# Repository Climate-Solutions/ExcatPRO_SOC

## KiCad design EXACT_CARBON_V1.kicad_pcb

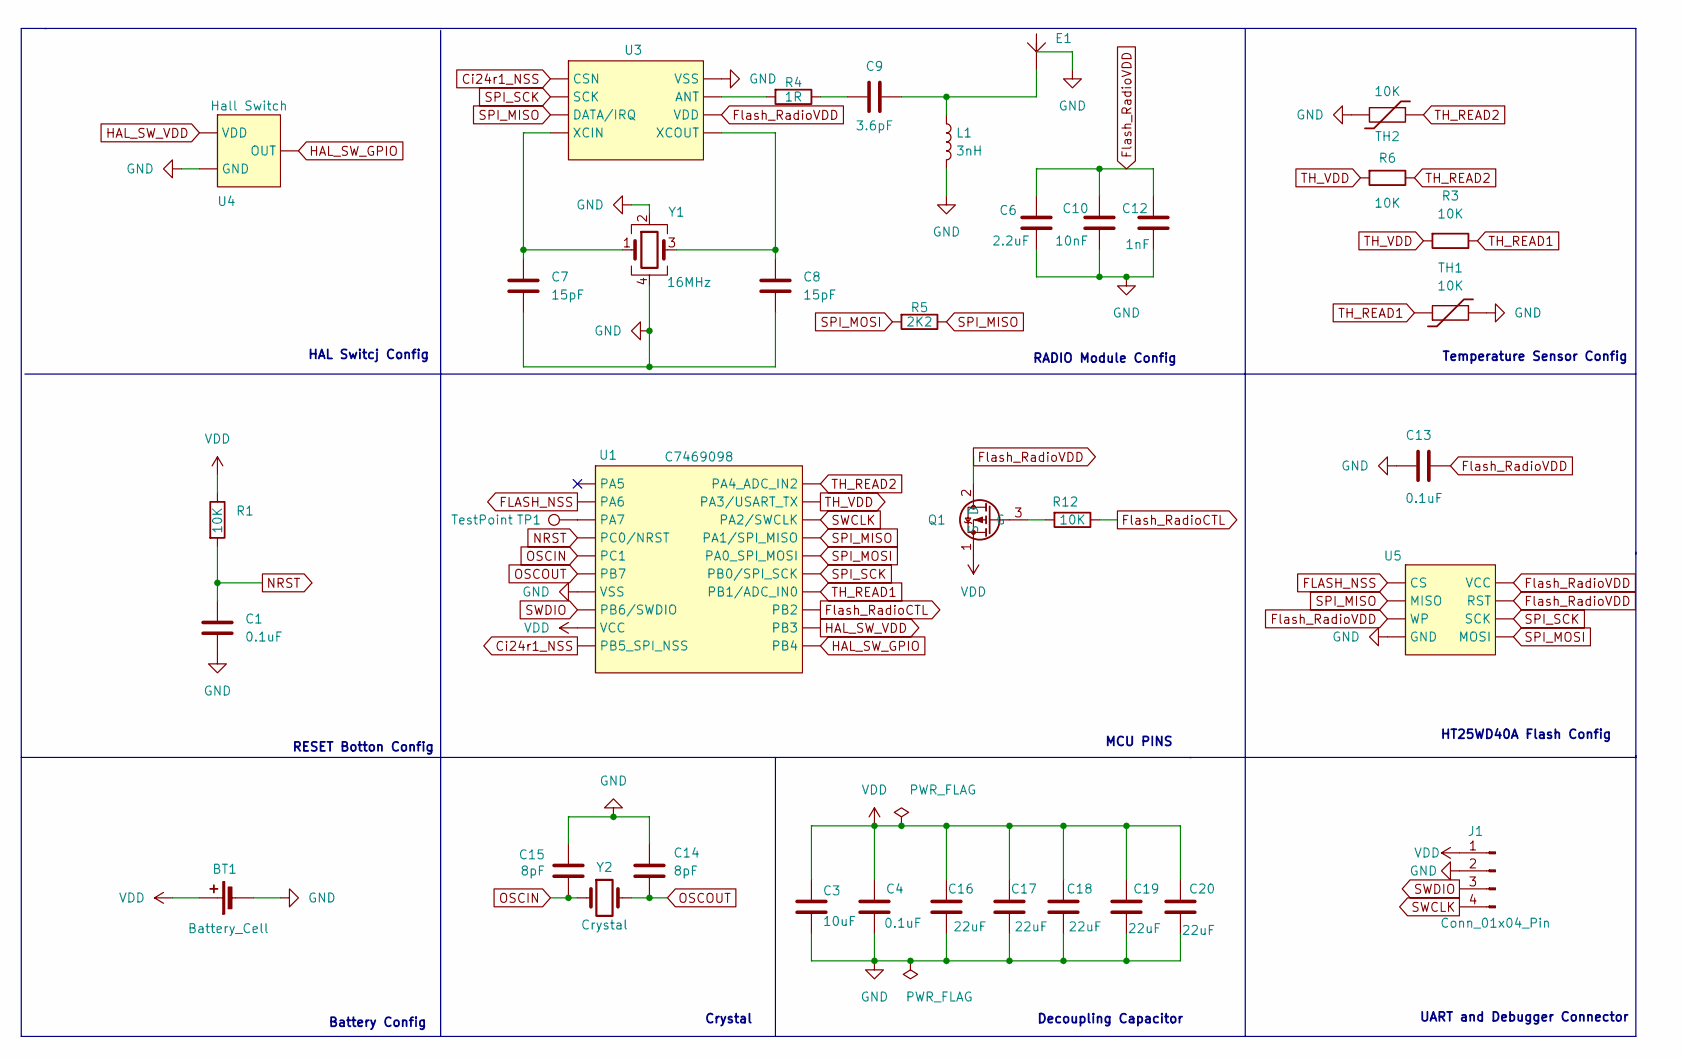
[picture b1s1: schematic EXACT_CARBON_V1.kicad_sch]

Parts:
BT1: Battery_Cell; CR2
C1, C4, C13: 0.1uF; C_0402_1005Metric_Pad0.74x0.62mm_HandSolder
C3: 10uF; C_0402_1005Metric_Pad0.74x0.62mm_HandSolder
C6: 2.2uF; C_0402_1005Metric_Pad0.74x0.62mm_HandSolder
C7, C8: 15pF; C_0402_1005Metric_Pad0.74x0.62mm_HandSolder
C9: 3.6pF; C_0402_1005Metric_Pad0.74x0.62mm_HandSolder
C10: 10nF; C_0402_1005Metric_Pad0.74x0.62mm_HandSolder
C12: 1nF; C_0402_1005Metric_Pad0.74x0.62mm_HandSolder
C14, C15: 8pF; C_0402_1005Metric_Pad0.74x0.62mm_HandSolder
C16, C17, C18, C19, C20: 22uF; C_0805_2012Metric
E1: PCB_Trace
J1: Conn_01x04_Pin; PinHeader_1x04_P2.00mm_Vertical
L1: 3nH; L_0402_1005Metric_Pad0.77x0.64mm_HandSolder
Q1: SOT-23
R1, R3, R6, R12: 10K; R_0402_1005Metric_Pad0.72x0.64mm_HandSolder
R4: 1R; R_0402_1005Metric
R5: 2K2; R_0402_1005Metric
TH1, TH2: 10K; R_0402_1005Metric_Pad0.72x0.64mm_HandSolder
TP1: TestPoint; TestPoint_Pad_D1.0mm
U1: C7469098; TSSOP-20_4.4x6.5mm_P0.65mm
U3: Ci24r1
U4: Hall Switch; HAL2041SO
U5: SOP-8_3.9x4.9mm_P1.27mm
Y1: 16MHz; Crystal_SMD_3225-4Pin_3.2x2.5mm
Y2: Crystal; Crystal_SMD_EuroQuartz_EQ161-2Pin_3.2x1.5mm

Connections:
Ci24r1_NSS: U1.10 (PB5_SPI_NSS), U3.1 (CSN)
FLASH_NSS: U1.2 (PA6), U5.1 (CS)
Flash_RadioCTL: R12.1, U1.13 (PB2)
Flash_RadioVDD: C6.1, C10.1, C12.1, C13.2, Q1.2 (D), U3.6 (VDD), U5.3 (WP), U5.7 (RST), U5.8 (VCC)
GND: BT1.2 (-), C1.2, C3.2, C4.2, C6.2, C7.2, C8.2, C10.2, C12.2, C13.1, C14.1, C15.1, C16.2, C17.2, C18.2, C19.2, C20.2, E1.1 (GND), J1.2, L1.2, TH1.2, TH2.2, U1.7 (VSS), U3.8 (VSS), U4.2 (GND), U5.4 (GND), Y1.2, Y1.4
HAL_SW_GPIO: U1.11 (PB4), U4.3 (OUT)
HAL_SW_VDD: U1.12 (PB3), U4.1 (VDD)
NRST: C1.1, R1.2, U1.4 (PC0/NRST)
unnamed: C9.1, R4.1
unnamed: C9.2, E1.2 (ANT), L1.1
unnamed: Q1.3 (G), R12.2
unnamed: TP1.1 (1_1), U1.3 (PA7)
unnamed: R4.2, U3.7 (ANT)
unnamed: C7.1, U3.4 (XCIN), Y1.1
unnamed: C8.1, U3.5 (XCOUT), Y1.3
OSCIN: C15.2, U1.5 (PC1), Y2.1
OSCOUT: C14.2, U1.6 (PB7), Y2.2
SPI_MISO: R5.1, U1.17 (PA1/SPI_MISO), U3.3 (DATA/IRQ), U5.2 (MISO)
SPI_MOSI: R5.2, U1.16 (PA0_SPI_MOSI), U5.5 (MOSI)
SPI_SCK: U1.15 (PB0/SPI_SCK), U3.2 (SCK), U5.6 (SCK)
SWCLK: J1.4, U1.18 (PA2/SWCLK)
SWDIO: J1.3, U1.8 (PB6/SWDIO)
TH_READ1: R3.1, TH1.1, U1.14 (PB1/ADC_IN0)
TH_READ2: R6.1, TH2.1, U1.20 (PA4_ADC_IN2)
TH_VDD: R3.2, R6.2, U1.19 (PA3/USART_TX)
VDD: BT1.1 (+), C3.1, C4.1, C16.1, C17.1, C18.1, C19.1, C20.1, J1.1, Q1.1 (S), R1.1, U1.9 (VCC)

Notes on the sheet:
MCU PINS
HAL Switcj Config
Decoupling Capacitor
UART and Debugger Connector
Crystal
Temperature Sensor Config
Battery Config
RADIO Module Config
RESET Botton Config
HT25WD40A Flash Config

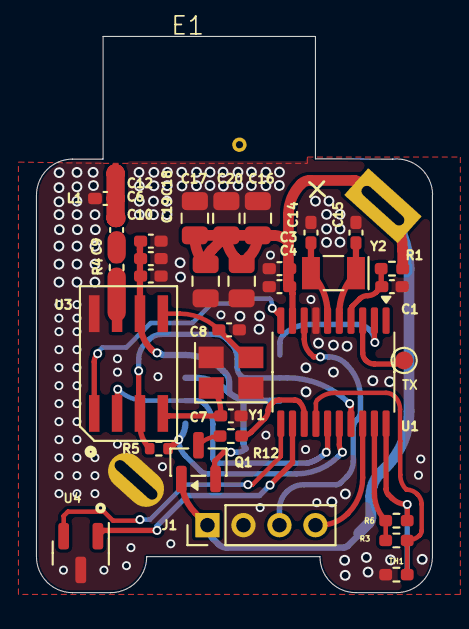
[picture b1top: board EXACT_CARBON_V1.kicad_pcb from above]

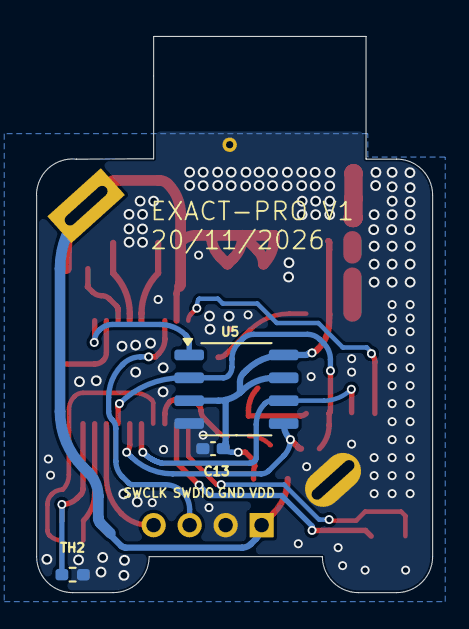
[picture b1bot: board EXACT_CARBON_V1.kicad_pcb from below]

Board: 2 copper layers, 22.0 x 30.9 mm, 37 parts (3 on the bottom side), 26 nets.
